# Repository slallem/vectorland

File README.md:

# vectorland
Vectrex related resources

## cartridge/PCB

PCB v1.00 : My first PCB batch, with few caveats:

- Holes spacing don't fit in original shells
- Solder point for 27C256 is way too small and hard to solder
- Missing cversion number
- Missing marking for parts 

PCB v1.01 (ideas / work in progress)
 
- 3 pin jumper selector instead of solder point
- Logo on back
- Version

## cartridge/shell

My 3D modeling of a Vectrex cartridge shell.

Few variants available (ZIF top, custom PCBs).

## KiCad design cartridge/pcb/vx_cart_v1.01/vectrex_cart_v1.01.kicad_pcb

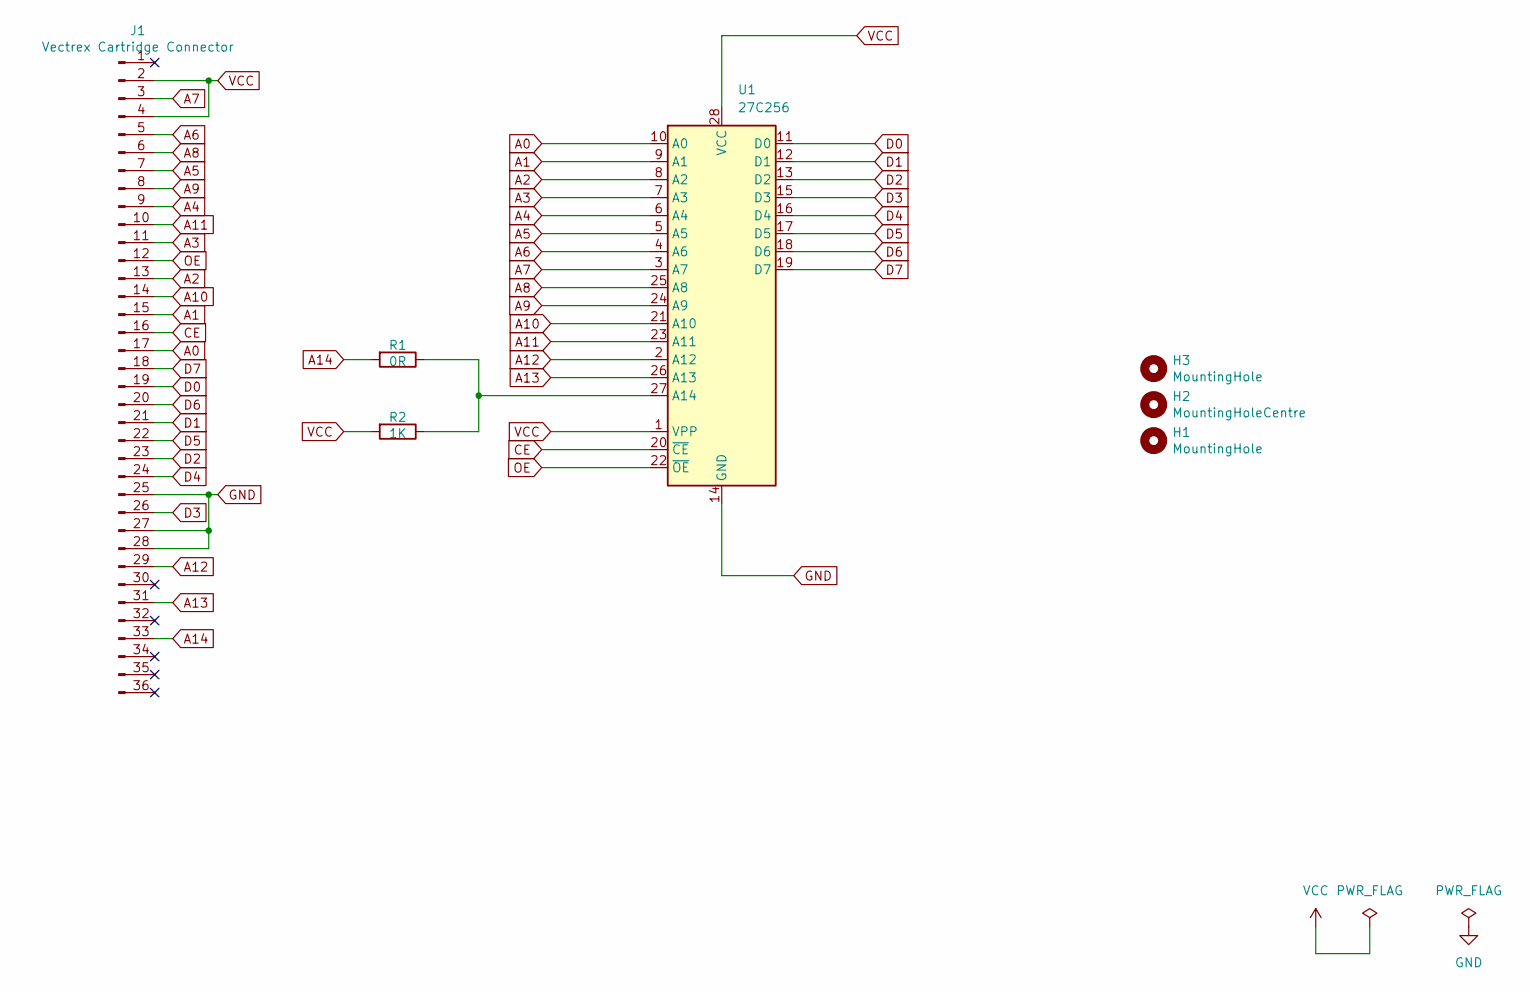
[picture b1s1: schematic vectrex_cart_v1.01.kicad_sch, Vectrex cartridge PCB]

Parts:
H1, H3: MountingHole; MountingHole_3.7mm
H2: MountingHoleCentre; MountingHole_5.3mm_M5
J1: Vectrex Cartridge Connector; VECTREX_CART
R1: 0R; R_Axial_DIN0204_L3.6mm_D1.6mm_P7.62mm_Horizontal
R2: 1K; R_Axial_DIN0204_L3.6mm_D1.6mm_P7.62mm_Horizontal
U1: 27C256; DIP-28_W15.24mm_LongPads

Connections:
A0: J1.17, U1.10 (A0)
A1: J1.15, U1.9 (A1)
A2: J1.13, U1.8 (A2)
A3: J1.11, U1.7 (A3)
A4: J1.9, U1.6 (A4)
A5: J1.7, U1.5 (A5)
A6: J1.5, U1.4 (A6)
A7: J1.3, U1.3 (A7)
A8: J1.6, U1.25 (A8)
A9: J1.8, U1.24 (A9)
A10: J1.14, U1.21 (A10)
A11: J1.10, U1.23 (A11)
A12: J1.29, U1.2 (A12)
A13: J1.31, U1.26 (A13)
A14: J1.33, R1.2
CE: J1.16, U1.20 (~CE)
D0: J1.19, U1.11 (D0)
D1: J1.21, U1.12 (D1)
D2: J1.23, U1.13 (D2)
D3: J1.26, U1.15 (D3)
D4: J1.24, U1.16 (D4)
D5: J1.22, U1.17 (D5)
D6: J1.20, U1.18 (D6)
D7: J1.18, U1.19 (D7)
GND: J1.25, J1.27, J1.28, U1.14 (GND)
unnamed: R1.1, R2.1, U1.27 (A14)
OE: J1.12, U1.22 (~OE)
VCC: J1.2, J1.4, R2.2, U1.1 (VPP), U1.28 (VCC)

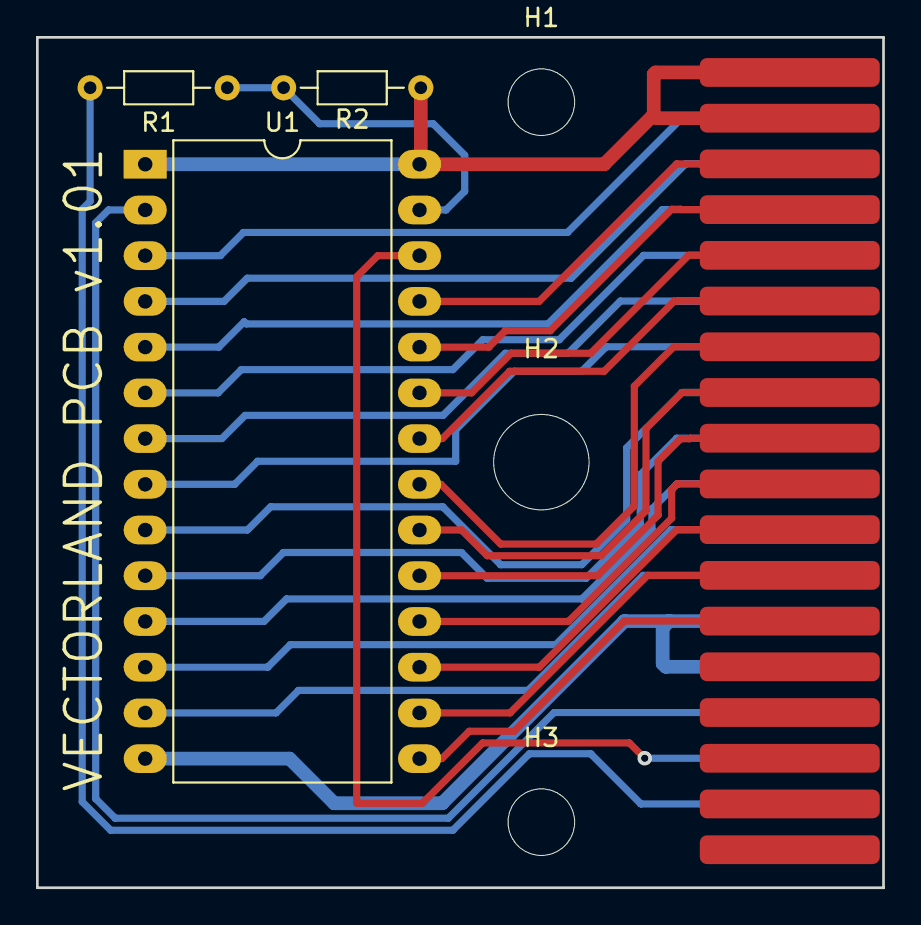
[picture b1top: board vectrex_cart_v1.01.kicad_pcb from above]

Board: 2 copper layers, 47.0 x 47.2 mm, 7 parts (0 on the bottom side), 28 nets.

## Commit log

2024-04-03 Initial version
2024-04-03 Documentation
2024-04-18 Introducing PCB v1.01
2024-04-18 Carte shell adjustment for PCB v1.00
2024-04-23 Cart PCB v1.01
